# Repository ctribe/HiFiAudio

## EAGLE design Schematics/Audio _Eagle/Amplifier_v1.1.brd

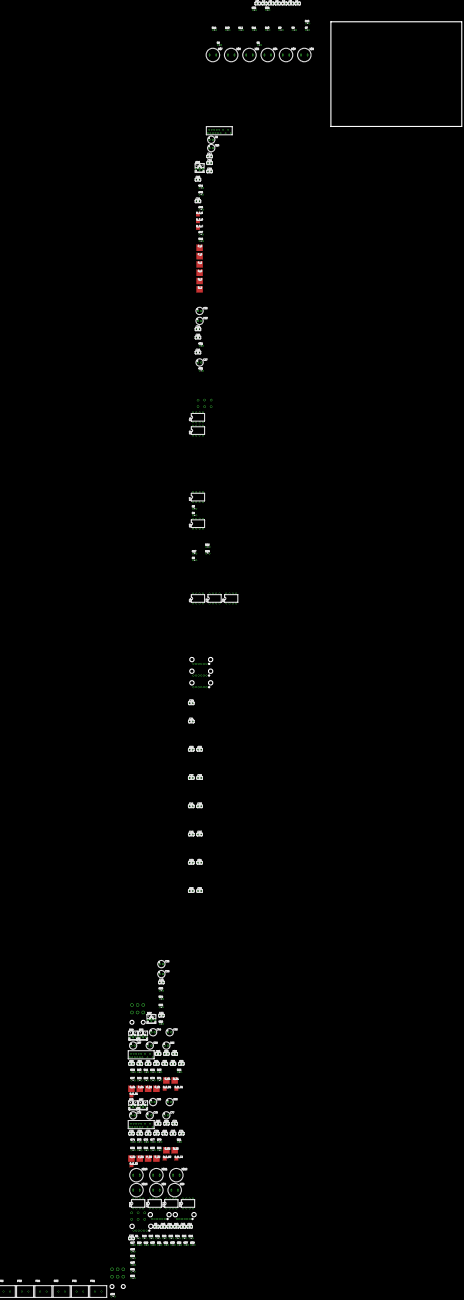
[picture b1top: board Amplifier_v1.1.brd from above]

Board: 2 copper layers, 100.0 x 80.0 mm, 227 parts (0 on the bottom side), 114 nets, no tracks yet.

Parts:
B_R_B, B_R_B1, B_R_B2: SMT_PAD_3MM
B_R_C, B_R_C1, B_R_C2: SMT_PAD_3MM
B_R_E, B_R_E1, B_R_E2: SMT_PAD_3MM
C1, C3, C4, C5, C6, C7, C8, C9, C10, C11, C12, C13, C14, C15: C025-024X044
C2, C16, C22, C23, C27, C36, C38, C44, C46, C57, C58, C62, C65, C66, C72, C73, C77: 100uF; E2,5-6
C17, C18, C24, C25, C26, C29, C31, C33, C35, C37, C39, C40, C41, C42, C43, C45, C47, C48, C49, C50, C51, C53, C55, C59, C60, C61, C63, C64, C67, C68, C74, C75, C76, C78, C79: 0.1uF; C025-024X044
C19, C20, C21, C52, C54, C56, C69, C70, C71: 22pF; C025-024X044
IC1, IC2, IC3, IC4, IC5, IC6, IC7, IC10, IC11, IC12, IC13: NE5532N; DIL08
N_B, N_B1, N_B2: SMT_PAD_5MM
N_D, N_D1, N_D2: SMT_PAD_5MM
N_S, N_S1, N_S2: SMT_PAD_5MM
PR1, PR2, PR3, PR4, PR5, PR6: 0.1; 2-1623788-1
P_B, P_B1, P_B2: SMT_PAD_5MM
P_D, P_D1, P_D2: SMT_PAD_5MM
P_S, P_S1, P_S2: SMT_PAD_5MM
R1, R2, R3, R4, R5, R6, R7, R8, R9, R10, R11, R12, R13, R14, R15, R16, R17, R18, R19, R20, R21, R22, R23, R24, R25, R26, R27, R28, R29, R30, R31, R32, R33, R34, R35, R36, R37, R38, R39, R88, R89, R90, R91, R92: 0204V
R43, R57, R58, R72, R73, R87: B25U
R44, R47, R48, R52, R53, R54, R55, R56, R59, R62, R63, R67, R68, R69, R70, R71, R74, R77, R78, R82, R83, R84, R85, R86: 1.2k; 0204V
R45, R60, R75: 500; 0204V
R46, R61, R76: 12k; 0204V
R51, R66, R81: 10; 0204V
U1, U2, U8: LME49830; NDN0015A
U$1, U$13, U$14, U$19, U$20, U$21: TONE_POT_2GANG
U$2, U$3, U$4, U$5, U$6, U$7, U$8, U$9, U$10, U$11, U$12, U$15: INDUCTOR
U$16, U$18: VOL_POT_2GANG
U$17, U$22: MOLEX_6P

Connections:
+12V: C31.2, C35.2, C36.+, C39.2, C43.2, C47.2, C51.2, C55.2, U$22.P$1
-12V: C29.1, C33.1, C37.1, C38.-, C41.1, C45.1, C49.1, C53.1, U$22.P$6
GND: C2.+, C3.1, C4.1, C7.2, C8.2, C10.1, C11.1, C14.2, C15.2, C16.-, C17.1, C18.2, C22.-, C23.+, C24.2, C25.1, C26.1, C27.-, C29.2, C31.1, C33.2, C35.1, C36.-, C37.2, C38.+, C39.1, C40.1, C41.2, C42.1, C43.1, C44.+, C45.2, C46.-, C47.1, C48.1, C49.2, C50.2, C51.1, C53.2, C55.1, C57.-, C58.+, C59.2, C60.1, C61.1, C62.-, C63.1, C64.1, C65.+, C66.-, C67.1, C68.2, C72.-, C73.+, C74.2, C75.1, C76.1, C77.-, C78.1, C79.1, IC1.4, IC1.5, IC1.8, IC2.4, IC2.5, IC2.8, IC3.4, IC3.5, IC3.8, IC4.4, IC4.8, IC5.4, IC5.8, IC6.4, IC6.8, IC7.3, IC7.4, IC7.8, IC10.5, IC11.5, IC12.3, IC13.5, R3.2, R5.1, R7.1, R10.1, R13.1, R15.1, R20.1, R23.1, R26.1, R28.1, R31.2, R38.1, R53.2, R68.2, R83.2, U1.3, U2.3, U8.3, U$3.1, U$4.1, U$5.1, U$6.1, U$9.1, U$10.1, U$11.1, U$12.1, U$17.P$2, U$17.P$4, U$17.P$6, U$22.P$4
unnamed: IC7.2, R2.2, U$16.1_1
unnamed: C1.1, IC7.1, U$16.1_2, U$16.1_3
unnamed: IC12.2, R1.2, U$18.1_1
unnamed: R48.2, U8.14
unnamed: C9.1, IC12.1, U$18.1_2, U$18.1_3
unnamed: IC1.2, R7.2, R8.1
unnamed: C4.2, IC1.3, R3.1, U$2.1
unnamed: B_R_C1.PAD, C54.2, R58.E, R59.1
unnamed: IC2.2, R12.1, R13.2
unnamed: R54.2, R88.2, R89.2, R90.2
unnamed: IC1.6, R6.2, R34.1
unnamed: C3.2, R4.2, U$2.2
unnamed: C5.2, R9.2, U$3.2
unnamed: C11.2, IC10.3, R31.1, U$8.1
unnamed: IC3.1, R16.1, R17.2
unnamed: C40.2, R53.1, R54.1, U8.4
unnamed: IC2.1, R11.1, R12.2
unnamed: IC2.6, R11.2, R35.1
unnamed: IC3.6, R16.2, R18.1
unnamed: B_R_B1.PAD, C54.1, R58.A, R58.S, R60.2
unnamed: IC3.7, R88.1, U$14.1_2, U$14.1_3
unnamed: C1.2, R4.1, R9.1, R14.1
unnamed: C7.1, R14.2, U$6.2, U$7.2
unnamed: R18.2, U$14.1_1
unnamed: IC10.6, R19.2, R29.1
unnamed: R2.1, U$22.P$3
unnamed: IC3.2, R5.2, R17.1
unnamed: C52.2, R59.2, U1.12
unnamed: C6.1, U$7.1
unnamed: C12.2, R22.2, U$9.2
unnamed: R55.1, R57.A, U8.5
unnamed: IC11.1, R24.1, R25.2
unnamed: IC11.6, R24.2, R30.1
unnamed: C14.1, R27.2, U$12.2, U$15.2
unnamed: C13.1, U$15.1
unnamed: C42.2, R55.2
unnamed: R29.2, U$19.1_1
unnamed: R39.1, R84.2, R91.2, R92.2
unnamed: B_R_E1.PAD, C52.1, C56.1, R60.1, U1.11
unnamed: R56.2, R57.E, R57.S
unnamed: IC11.7, R91.1, U$20.1_2, U$20.1_3
unnamed: R30.2, U$20.1_1
unnamed: IC10.1, R19.1, R21.2
unnamed: C10.2, R32.2, U$8.2
unnamed: IC10.2, R20.2, R21.1
unnamed: IC11.2, R25.1, R26.2
unnamed: IC13.1, R33.1, R36.2
unnamed: C56.2, U1.6
unnamed: IC13.6, R33.2, R37.1
unnamed: IC13.7, R92.1, U$21.1_2, U$21.1_3
unnamed: R62.2, U1.13
unnamed: P_B1.PAD, R61.2, R63.1
unnamed: R34.2, U$1.1_1
unnamed: IC1.7, R90.1, U$1.1_2, U$1.1_3
unnamed: IC2.7, R89.1, U$13.1_2, U$13.1_3
unnamed: R35.2, U$13.1_1
unnamed: R37.2, U$21.1_1
unnamed: IC13.2, R36.1, R38.2
unnamed: C13.2, C15.1, IC13.3, R28.2, U$11.2
unnamed: C9.2, R22.1, R27.1, R32.1
unnamed: C12.1, IC11.3, R23.2, U$10.2
unnamed: N_B1.PAD, R61.1, R62.1
unnamed: C5.1, IC2.3, R10.2, U$4.2
unnamed: IC10.7, R39.2, R69.2, U$19.1_2, U$19.1_3
unnamed: B_R_C.PAD, C20.2, R43.E, R44.1
unnamed: C21.2, U8.6
unnamed: B_R_E.PAD, C19.1, C21.1, R45.1, U8.11
unnamed: B_R_B.PAD, C20.1, R43.A, R43.S, R45.2
unnamed: C19.2, R44.2, U8.12
unnamed: R47.2, U8.13
unnamed: PR1.P$4, P_S1.PAD
unnamed: P_B.PAD, R46.2, R48.1
unnamed: N_B.PAD, R46.1, R47.1
unnamed: PR4.P$4, P_S.PAD
unnamed: PR3.P$4, PR4.P$3, R51.2, R56.1, U8.8, U$17.P$1
unnamed: PR1.P$3, PR2.P$4, R66.2, R71.1, U1.8, U$17.P$3
unnamed: C61.2, R66.1
unnamed: C62.+, R67.2, U1.2
unnamed: R63.2, U1.14
unnamed: C63.2, R68.1, R69.1, U1.4
unnamed: C64.2, R70.2
unnamed: R70.1, R72.A, U1.5
unnamed: R71.2, R72.E, R72.S
unnamed: C26.2, R51.1
unnamed: C27.+, R52.2, U8.2
unnamed: B_R_C2.PAD, C70.2, R73.E, R74.1
unnamed: B_R_B2.PAD, C70.1, R73.A, R73.S, R75.2
unnamed: IC1.1, R6.1, R8.2
unnamed: C69.2, R74.2, U2.12
unnamed: B_R_E2.PAD, C69.1, C71.1, R75.1, U2.11
unnamed: C71.2, U2.6
unnamed: R77.2, U2.13
unnamed: P_B2.PAD, R76.2, R78.1
unnamed: N_B2.PAD, R76.1, R77.1
unnamed: PR5.P$4, P_S2.PAD
unnamed: PR5.P$3, PR6.P$4, R81.2, R86.1, U2.8, U$17.P$5
unnamed: C76.2, R81.1
unnamed: C77.+, R82.2, U2.2
unnamed: R78.2, U2.14
unnamed: C78.2, R83.1, R84.1, U2.4
unnamed: C79.2, R85.2
unnamed: R85.1, R87.A, U2.5
unnamed: R86.2, R87.E, R87.S
unnamed: C6.2, C8.1, IC3.3, R15.2, U$5.2
unnamed: N_S1.PAD, PR2.P$3
unnamed: R1.1, U$22.P$5
unnamed: N_S2.PAD, PR6.P$3
unnamed: N_S.PAD, PR3.P$3
V+: C16.+, C18.1, C46.+, C50.1, C66.+, C68.1, U1.15, U2.15, U8.15
V-: C2.-, C17.2, C23.-, C25.2, C44.-, C48.2, C58.-, C60.2, C65.-, C67.2, C73.-, C75.2, IC10.4, IC11.4, IC12.4, IC13.4, N_D.PAD, N_D1.PAD, N_D2.PAD, U1.10, U2.10, U8.10
VCC: C22.+, C24.1, C57.+, C59.1, C72.+, C74.1, IC10.8, IC11.8, IC12.8, IC13.8, P_D.PAD, P_D1.PAD, P_D2.PAD

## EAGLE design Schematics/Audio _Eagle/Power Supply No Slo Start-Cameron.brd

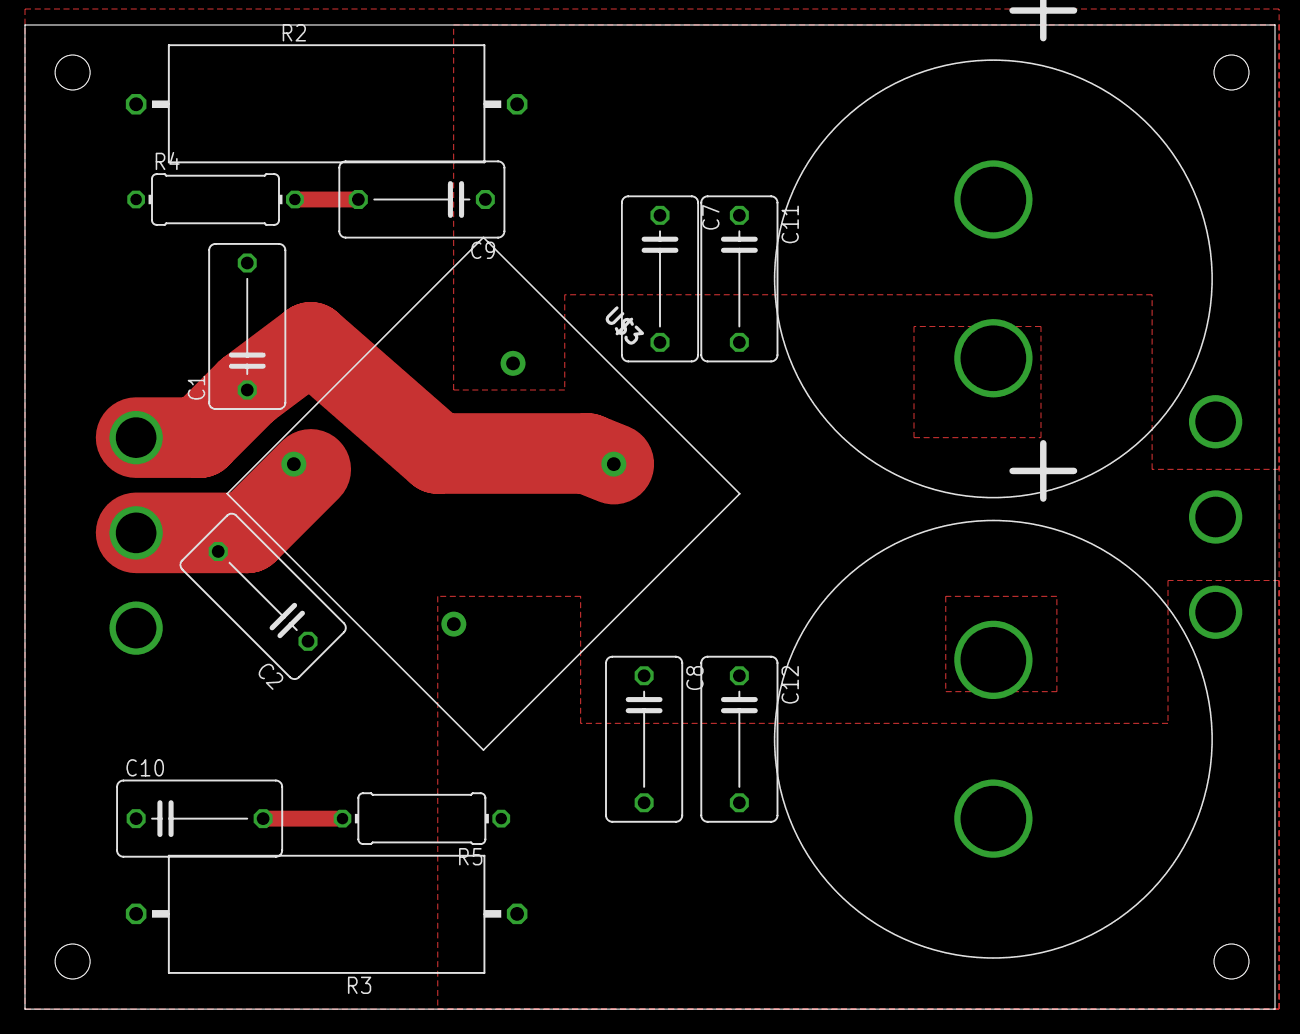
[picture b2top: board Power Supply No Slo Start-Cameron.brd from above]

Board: 2 copper layers, 100.0 x 78.7 mm, 17 parts (0 on the bottom side), 7 nets.

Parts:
C1, C2, C7, C8, C9, C10: 0.1uF; C102-064X133
C11, C12: 1uF; C102-064X133
C13, C19: 15,000uF; PHI-35
P1, P2: 3PIN_3.25MM; 3PIN_SCREW_EYELET
R2, R3: 2k; VTA52
R4, R5: 1; 0411/12
U$3: GBPC3510W

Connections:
AC1: C1.1, P1.P$1, U$3.AC1
AC2: C2.2, P1.P$2, U$3.AC2
GND: C1.2, C2.1, C7.2, C8.1, C10.1, C11.2, C12.1, C13.+, C19.-, P1.P$3, P2.P$2, R2.1, R3.2, R4.1
unnamed: C10.2, R5.2
unnamed: C9.2, R4.2
VCC: C7.1, C9.1, C11.1, C19.+, P2.P$1, R2.2, U$3.V+
VEE: C8.2, C12.2, C13.-, P2.P$3, R3.1, R5.1, U$3.V-

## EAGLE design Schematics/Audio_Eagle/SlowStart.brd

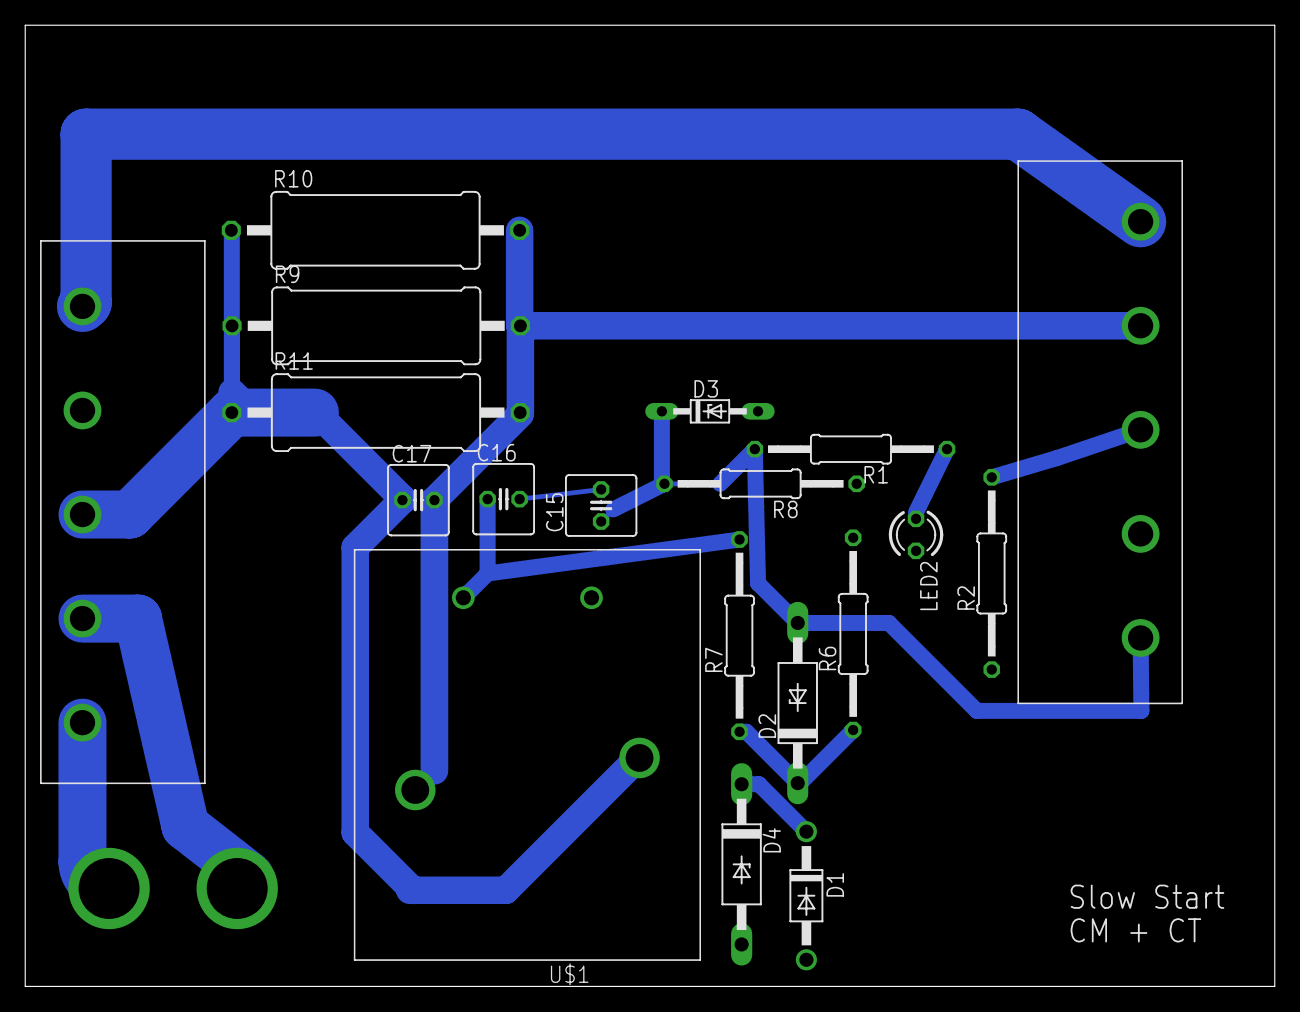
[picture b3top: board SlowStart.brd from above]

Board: 2 copper layers, 99.1 x 76.2 mm, 20 parts (0 on the bottom side), 11 nets.

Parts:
C15, C16: 1uF; C025-060X050
C17: 0.01uF; C025-060X050
D1: 1N4004; DO41-10
D2: 22V; P1Z12
D3: 3.9V; DO34Z7
D4: 28V; P1Z12
LED2: TLLG4400; LED3MM
R1, R8: 10k; 0207/15
R2: 100; 0207/15
R6: 560; 0207/15
R7: 390; 0207/15
R9, R10, R11: 68; 0617/22
U$1: T9AS1D; RELAY_CM
U$2, U$3: SCREW_TERMINAL_5
U$4: FUSE; FUSE_PADS

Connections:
GND: C15.2, C16.2, D1.A, D3.A, D4.A, LED2.K, R2.1, R8.1, U$1.COIL+, U$2.P$2
unnamed: LED2.A, R1.1
unnamed: U$2.P$6, U$4.P$2
unnamed: R2.2, U$3.P$3
unnamed: U$2.P$5, U$4.P$1
unnamed: C17.2, R9.2, R10.2, R11.2, U$1.NO, U$3.P$5
unnamed: C16.1, D1.C, D4.C, R7.2, U$1.COIL-
unnamed: D2.C, R6.1, R7.1
unnamed: C15.1, D2.A, D3.C, R1.2, R8.2, U$3.P$4
VAC+: U$2.P$4, U$3.P$6
VAC-: C17.1, R9.1, R10.1, R11.1, U$1.COM, U$2.P$3

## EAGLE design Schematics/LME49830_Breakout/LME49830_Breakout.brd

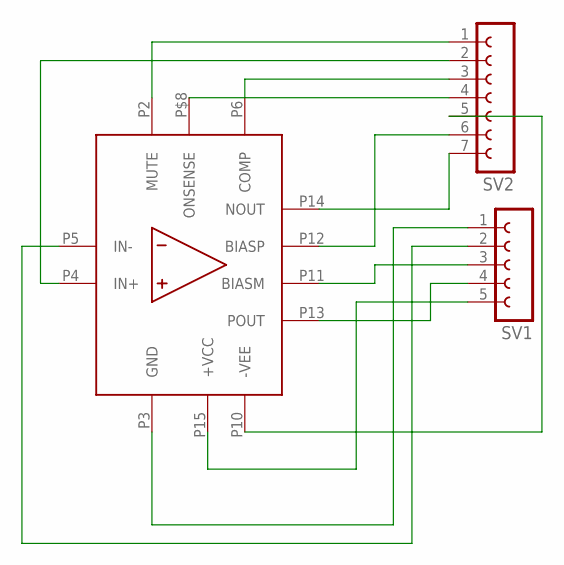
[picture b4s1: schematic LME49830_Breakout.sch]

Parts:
SV1: FE05-1
SV2: FE07-1; FE07
U$1: LME49830; NDN0015A

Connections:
unnamed: SV1.1, U$1.P3 (GND)
unnamed: SV1.2, U$1.P5 (IN-)
unnamed: SV1.3, U$1.P11 (BIASM)
unnamed: SV1.4, U$1.P13 (POUT)
unnamed: SV1.5, U$1.P15 (+VCC)
unnamed: SV2.1, U$1.P2 (MUTE)
unnamed: SV2.2, U$1.P4 (IN+)
unnamed: SV2.3, U$1.P6 (COMP)
unnamed: SV2.4, U$1.P$8 (ONSENSE)
unnamed: SV2.5, U$1.P10 (-VEE)
unnamed: SV2.6, U$1.P12 (BIASP)
unnamed: SV2.7, U$1.P14 (NOUT)

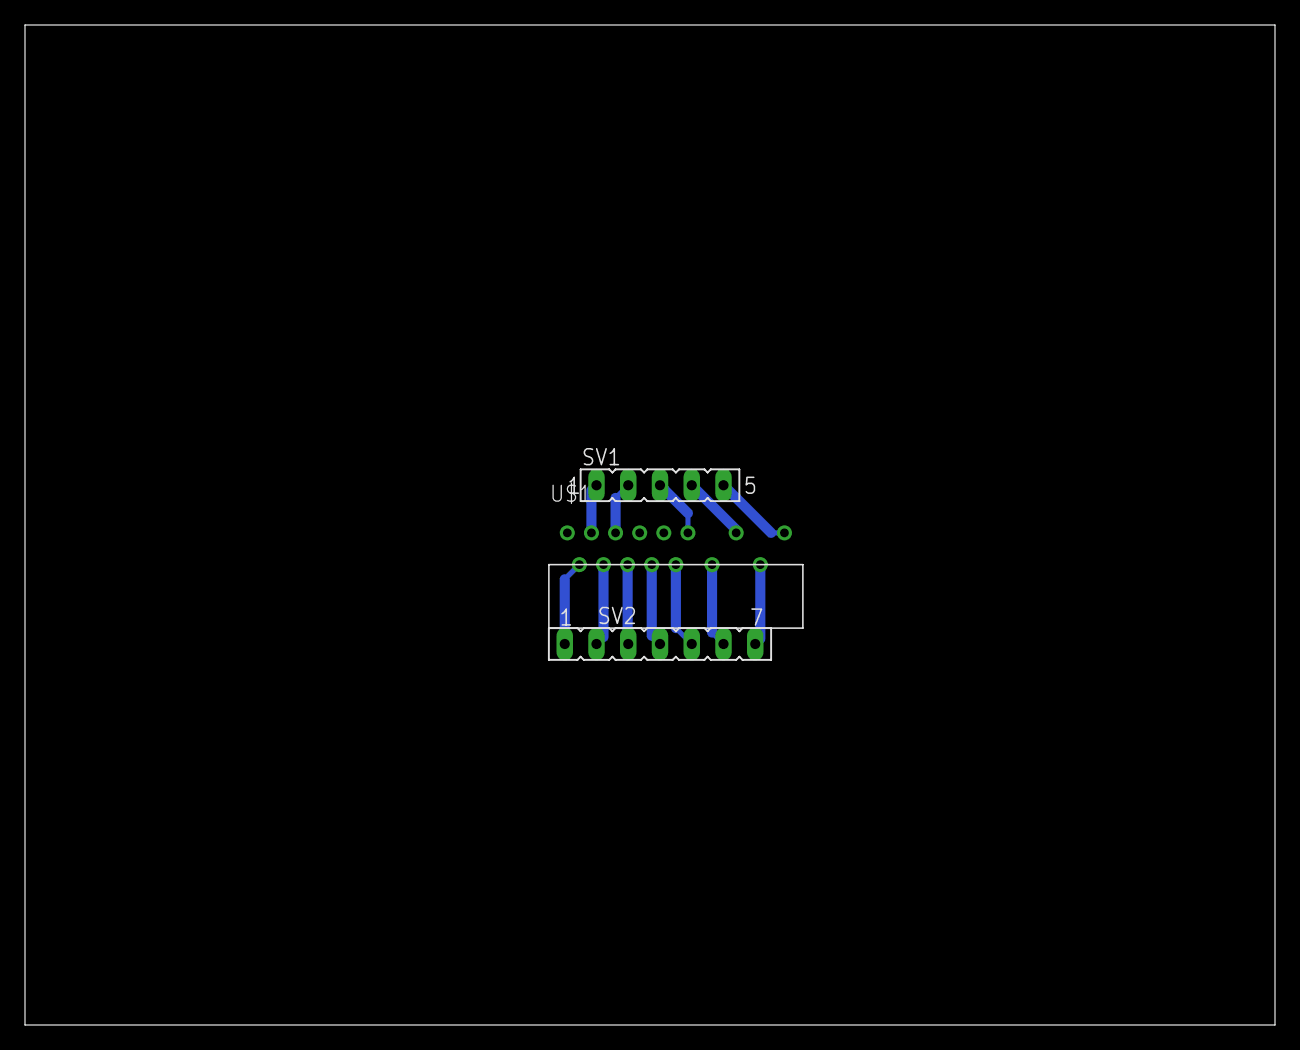
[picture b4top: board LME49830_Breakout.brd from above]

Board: 2 copper layers, 100.0 x 80.0 mm, 3 parts (0 on the bottom side), 12 nets.

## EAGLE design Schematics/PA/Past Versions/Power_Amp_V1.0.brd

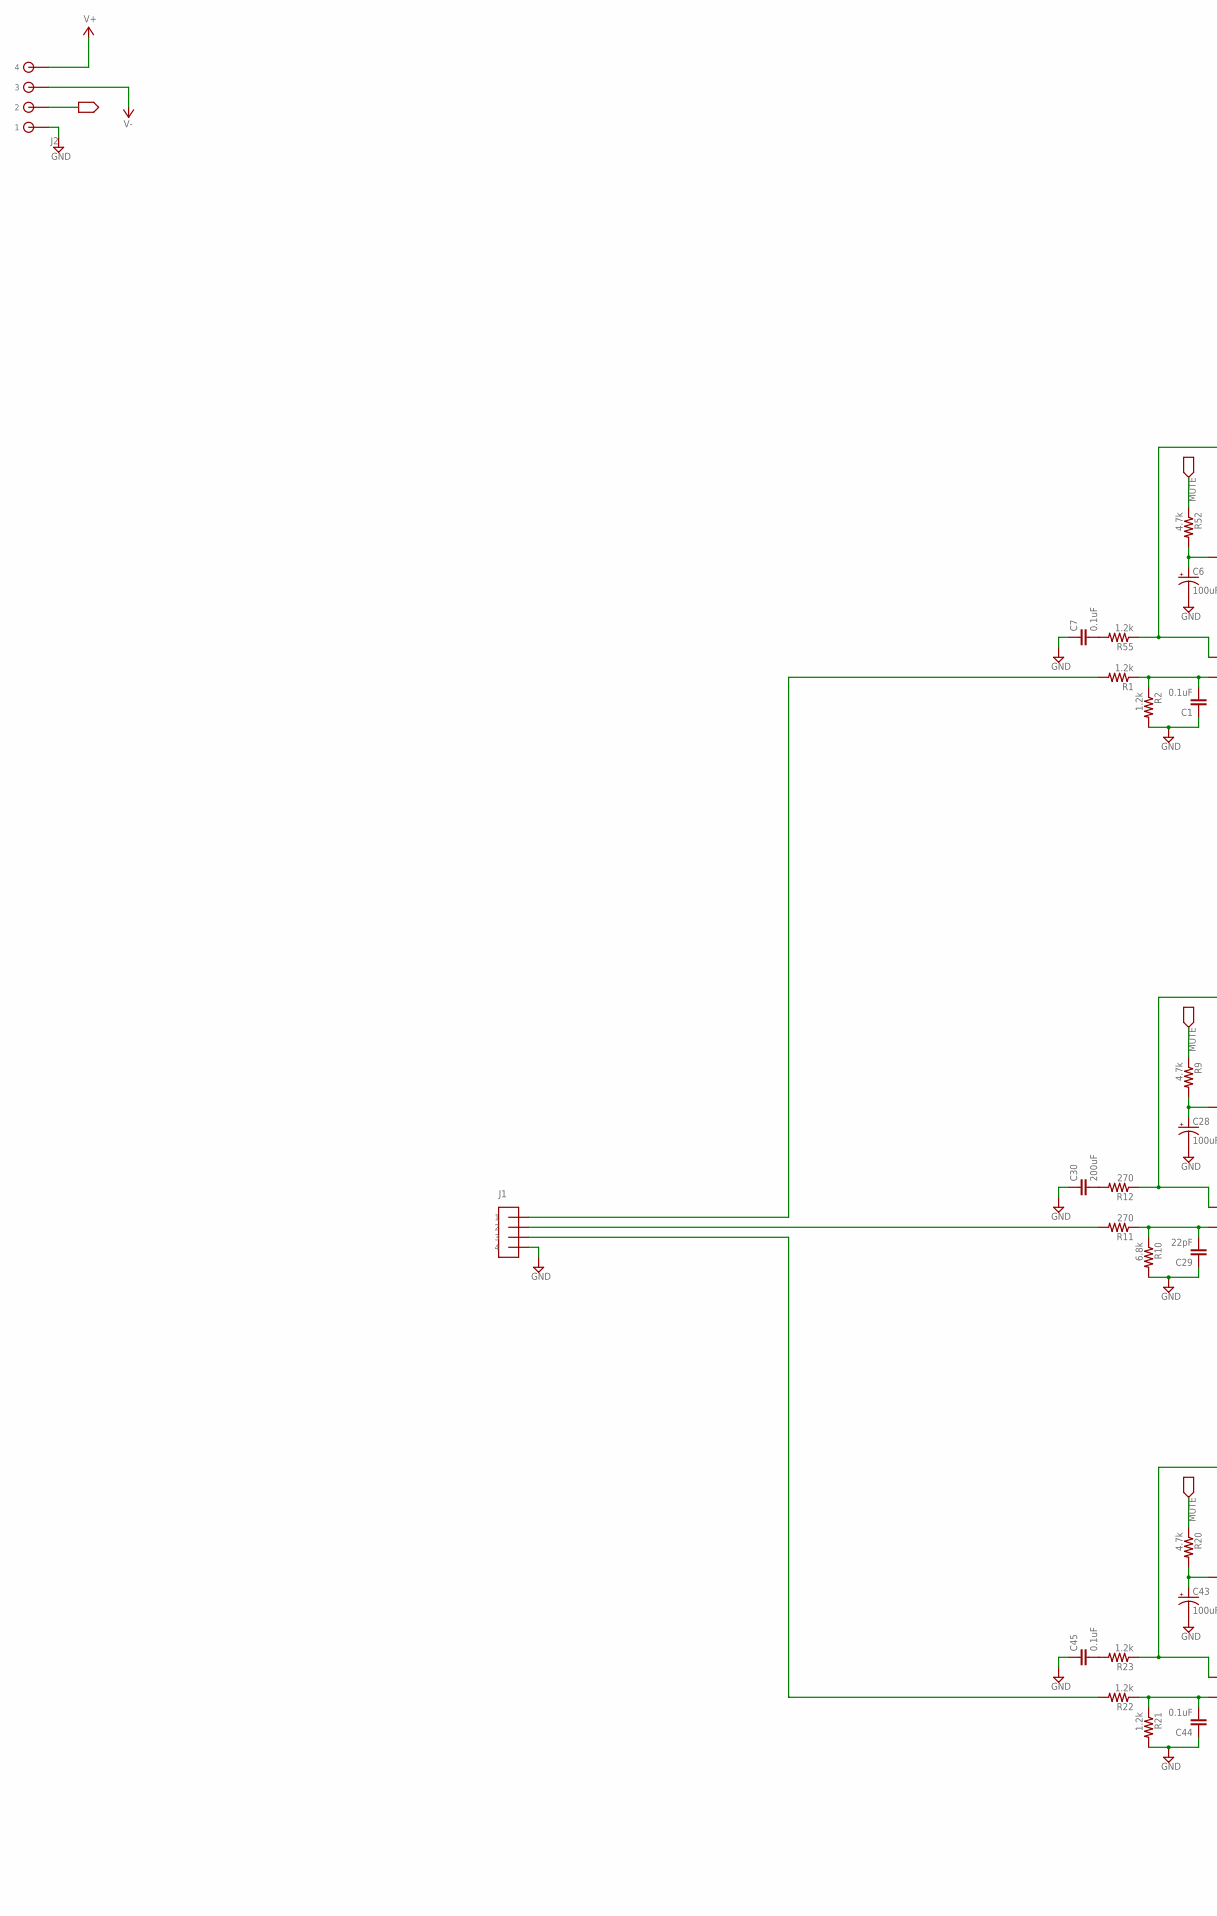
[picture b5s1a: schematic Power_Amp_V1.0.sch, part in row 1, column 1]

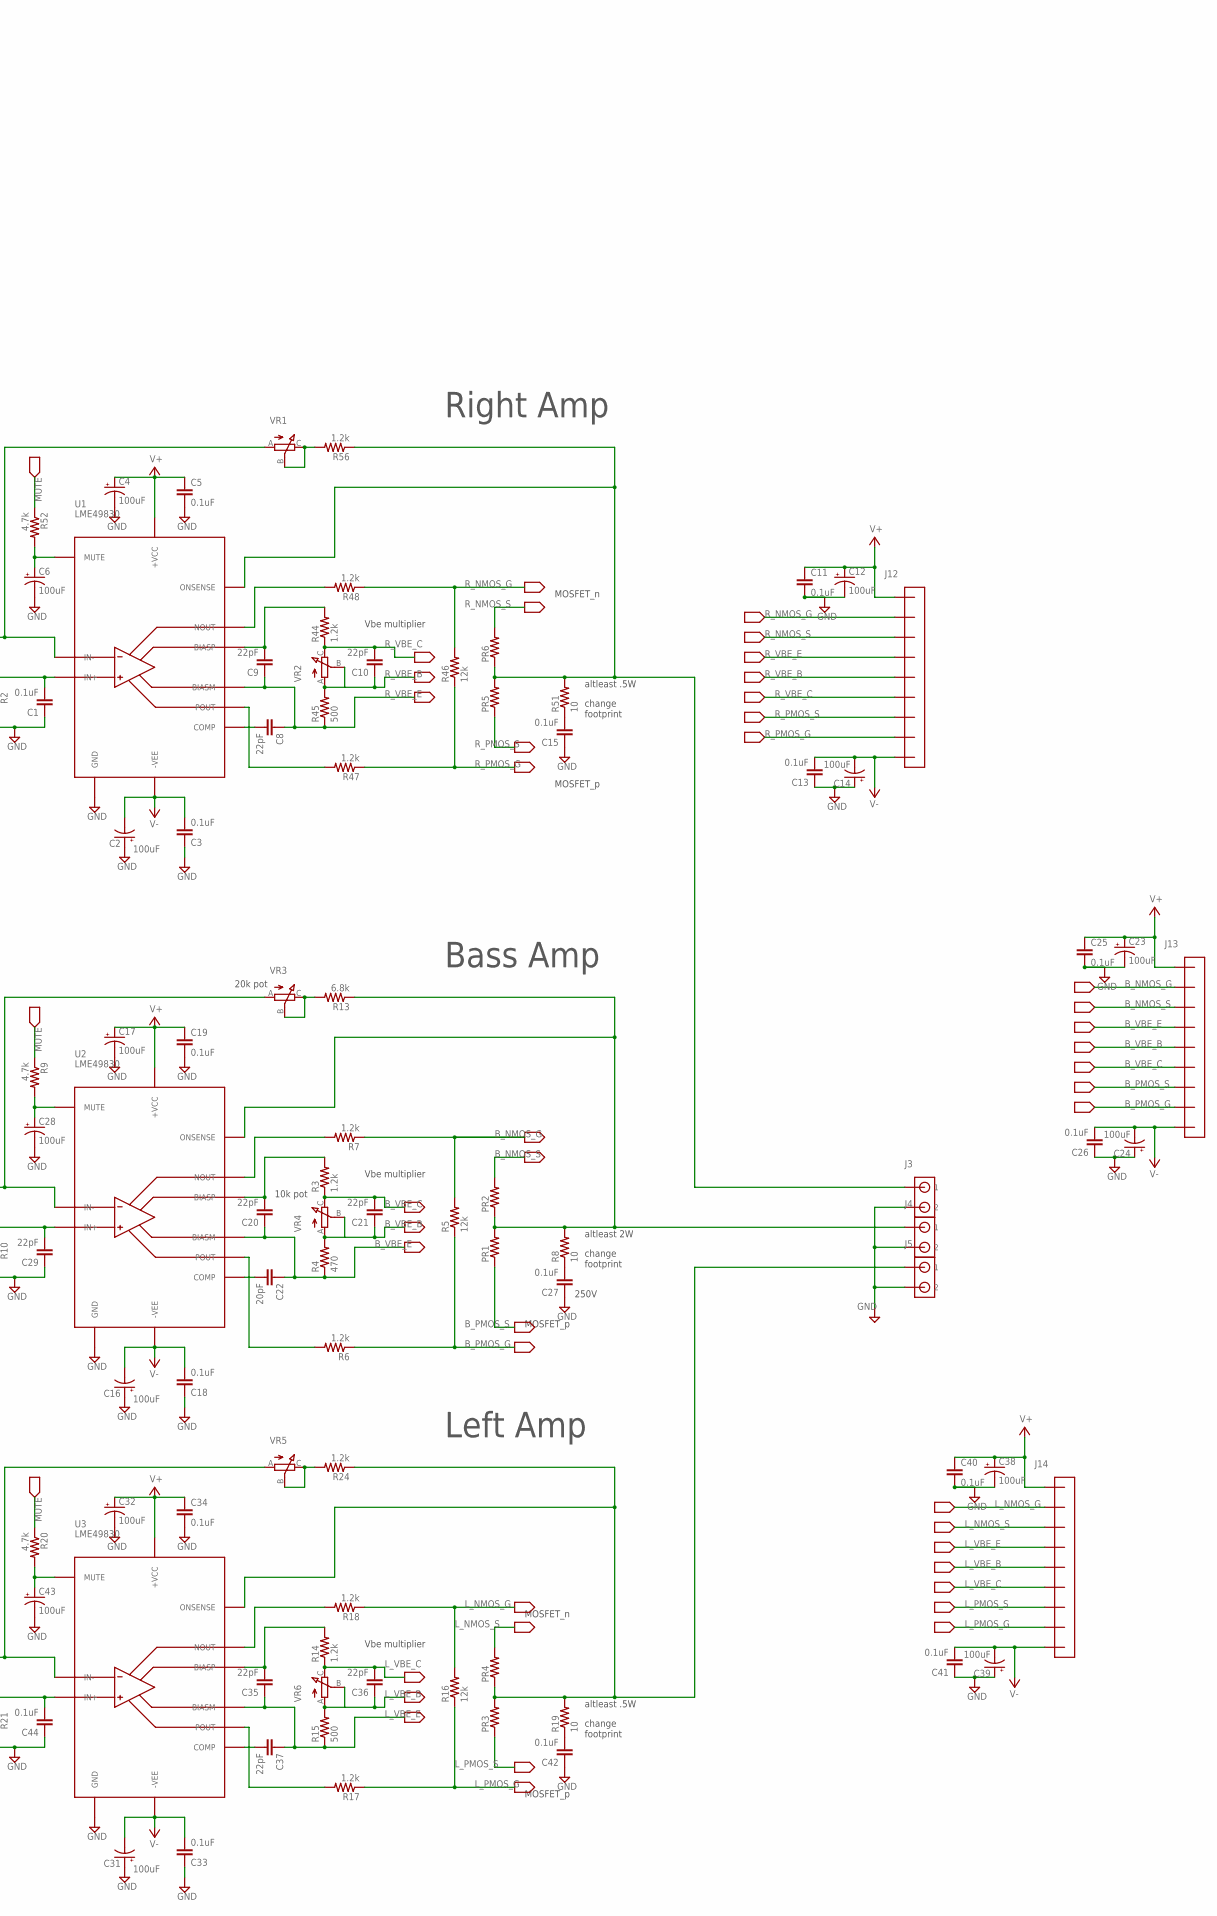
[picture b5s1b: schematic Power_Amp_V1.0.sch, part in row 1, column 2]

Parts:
C1, C3, C5, C7, C11, C13, C15, C18, C19, C25, C26, C27, C33, C34, C40, C41, C42, C44, C45: 0.1uF; C050-024X044
C2, C4, C6, C12, C14, C16, C17, C23, C24, C28, C31, C32, C38, C39, C43: 100uF; E2,5-6
C8, C9, C10, C20, C21, C29, C35, C36, C37: 22pF; C050-024X044
C22: 20pF; C050-024X044
C30: 200uF; C050-024X044
J1: 4_PIN_AMPCONN; 4_PIN_AMPCON
J2: 1984633
J3, J4, J5: 2TERMINAL_SPEAKER
J12, J13, J14: 1725724
PR1, PR2, PR3, PR4, PR5, PR6: R-US_0617/5V; 0617V
R1, R2, R3, R6, R7, R14, R17, R18, R21, R22, R23, R24, R44, R47, R48, R55, R56: 1.2k; 0204V
R4: 470; 0204V
R5, R16, R46: 12k; 0204V
R8, R19, R51: 10; 0309V
R9, R20, R52: 4.7k; 0204V
R10, R13: 6.8k; 0204V
R11, R12: 270; 0204V
R15, R45: 500; 0204V
U1, U2, U3: LME49830; NDN0015A
VR1, VR2, VR3, VR4, VR5, VR6: EVM2W

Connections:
BASS_IN: J1.2, R11.2
BASS_OUT: J4.P$1 (1), PR1.2, PR2.1, R8.2, R13.1, U2.P$8 (ONSENSE)
B_NMOS_G: J13.P$2 (2), R5.2, R7.1
B_NMOS_S: J13.P$3 (3), PR2.2
B_PMOS_G: J13.P$8 (8), R5.1, R6.1
B_PMOS_S: J13.P$7 (7), PR1.1
B_VBE_B: C21.1, J13.P$5 (5), R4.2, VR4.A, VR4.B
B_VBE_C: C21.2, J13.P$6 (6), R3.1, VR4.C
B_VBE_E: C20.1, C22.1, J13.P$4 (4), R4.1, U2.P11 (BIASM)
GND: C1.1, C2.+, C3.1, C4.-, C5.2, C6.-, C7.1, C11.2, C12.-, C13.1, C14.+, C15.1, C16.+, C17.-, C18.1, C19.2, C23.-, C24.+, C25.2, C26.1, C27.1, C28.-, C29.1, C30.1, C31.+, C32.-, C33.1, C34.2, C38.-, C39.+, C40.2, C41.1, C42.1, C43.-, C44.1, C45.1, J1.4, J2.P$1 (1), J3.P$2 (2), J4.P$2 (2), J5.P$2 (2), R2.2, R10.2, R21.2, U1.P3 (GND), U2.P3 (GND), U3.P3 (GND)
LEFT_IN: J1.3, R22.2
LEFT_OUT: J5.P$1 (1), PR3.2, PR4.1, R19.2, R24.1, U3.P$8 (ONSENSE)
L_NMOS_G: J14.P$2 (2), R16.2, R18.1
L_NMOS_S: J14.P$3 (3), PR4.2
L_PMOS_G: J14.P$8 (8), R16.1, R17.1
L_PMOS_S: J14.P$7 (7), PR3.1
L_VBE_B: C36.1, J14.P$5 (5), R15.2, VR6.A, VR6.B
L_VBE_C: C36.2, J14.P$6 (6), R14.1, VR6.C
L_VBE_E: C35.1, C37.1, J14.P$4 (4), R15.1, U3.P11 (BIASM)
MUTE: J2.P$2 (2), R9.1, R20.1, R52.1
unnamed: C20.2, R3.2, U2.P12 (BIASP)
unnamed: R48.2, U1.P14 (NOUT)
unnamed: C22.2, U2.P6 (COMP)
unnamed: R6.2, U2.P13 (POUT)
unnamed: C27.2, R8.1
unnamed: C28.+, R9.2, U2.P2 (MUTE)
unnamed: R7.2, U2.P14 (NOUT)
unnamed: C1.2, R1.1, R2.1, U1.P4 (IN+)
unnamed: C29.2, R10.1, R11.1, U2.P4 (IN+)
unnamed: C30.2, R12.2
unnamed: R12.1, U2.P5 (IN-), VR3.A
unnamed: R13.2, VR3.B, VR3.C
unnamed: C35.2, R14.2, U3.P12 (BIASP)
unnamed: C37.2, U3.P6 (COMP)
unnamed: R17.2, U3.P13 (POUT)
unnamed: R55.1, U1.P5 (IN-), VR1.A
unnamed: C42.2, R19.1
unnamed: C7.2, R55.2
unnamed: C43.+, R20.2, U3.P2 (MUTE)
unnamed: R18.2, U3.P14 (NOUT)
unnamed: C44.2, R21.1, R22.1, U3.P4 (IN+)
unnamed: R56.2, VR1.B, VR1.C
unnamed: C45.2, R23.2
unnamed: R23.1, U3.P5 (IN-), VR5.A
unnamed: R24.2, VR5.B, VR5.C
unnamed: C8.2, U1.P6 (COMP)
unnamed: C9.2, R44.2, U1.P12 (BIASP)
unnamed: R47.2, U1.P13 (POUT)
unnamed: C15.2, R51.1
unnamed: C6.+, R52.2, U1.P2 (MUTE)
RIGHT_IN: J1.1, R1.2
RIGHT_OUT: J3.P$1 (1), PR5.2, PR6.1, R51.2, R56.1, U1.P$8 (ONSENSE)
R_NMOS_G: J12.P$2 (2), R46.2, R48.1
R_NMOS_S: J12.P$3 (3), PR6.2
R_PMOS_G: J12.P$8 (8), R46.1, R47.1
R_PMOS_S: J12.P$7 (7), PR5.1
R_VBE_B: C10.1, J12.P$5 (5), R45.2, VR2.A, VR2.B
R_VBE_C: C10.2, J12.P$6 (6), R44.1, VR2.C
R_VBE_E: C8.1, C9.1, J12.P$4 (4), R45.1, U1.P11 (BIASM)
V+: C4.+, C5.1, C11.1, C12.+, C17.+, C19.1, C23.+, C25.1, C32.+, C34.1, C38.+, C40.1, J2.P$4 (4), J12.P$1 (1), J13.P$1 (1), J14.P$1 (1), U1.P15 (+VCC), U2.P15 (+VCC), U3.P15 (+VCC)
V-: C2.-, C3.2, C13.2, C14.-, C16.-, C18.2, C24.-, C26.2, C31.-, C33.2, C39.-, C41.2, J2.P$3 (3), J12.P$9 (9), J13.P$9 (9), J14.P$9 (9), U1.P10 (-VEE), U2.P10 (-VEE), U3.P10 (-VEE)

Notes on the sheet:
Vbe multiplier
MOSFET_n
MOSFET_p
change footprint
Right Amp
altleast .5W
Bass Amp
altleast 2W
Left Amp
20k pot
10k pot
250V

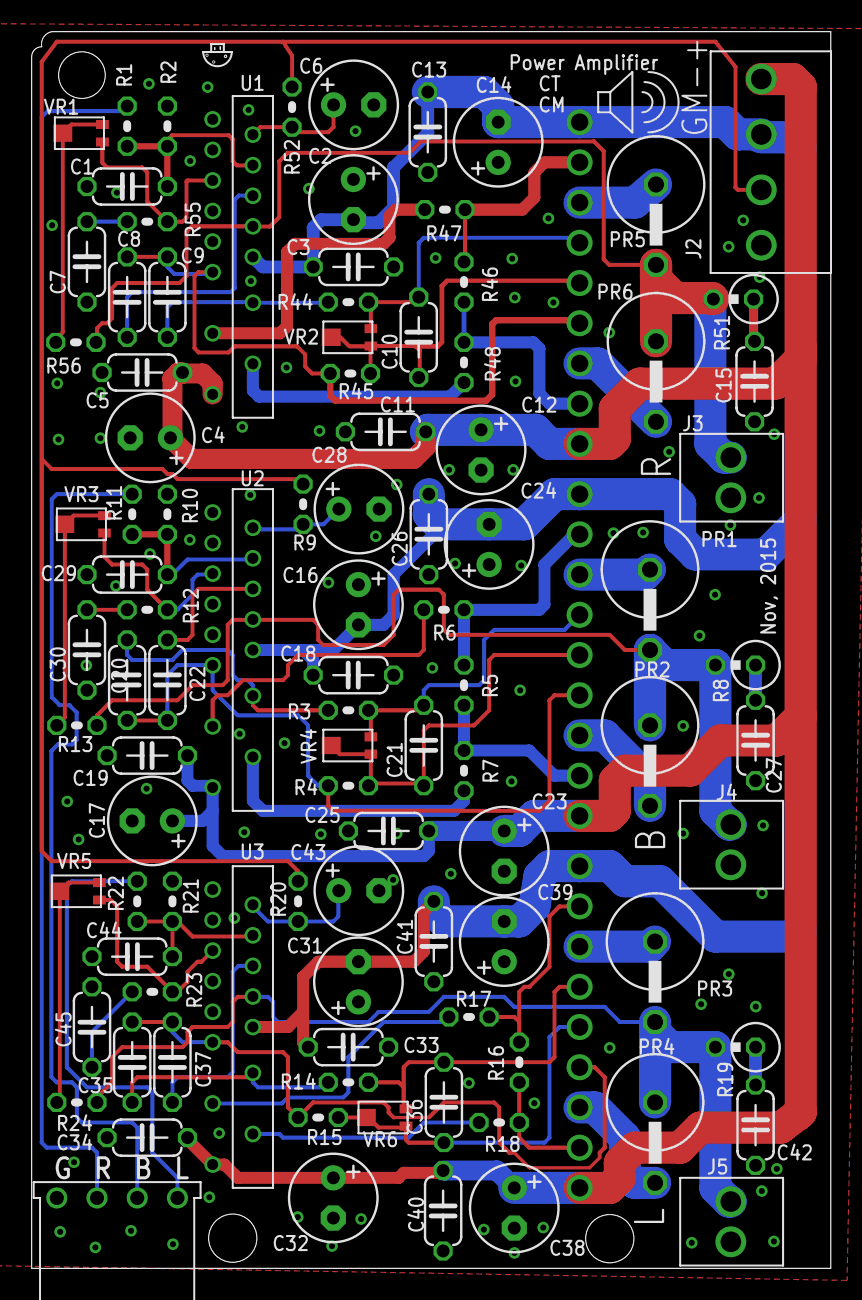
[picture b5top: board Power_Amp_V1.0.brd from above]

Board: 2 copper layers, 50.5 x 78.1 mm, 103 parts (0 on the bottom side), 61 nets.

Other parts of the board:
U$17: MUSHROOM
U$48: SPEAKER

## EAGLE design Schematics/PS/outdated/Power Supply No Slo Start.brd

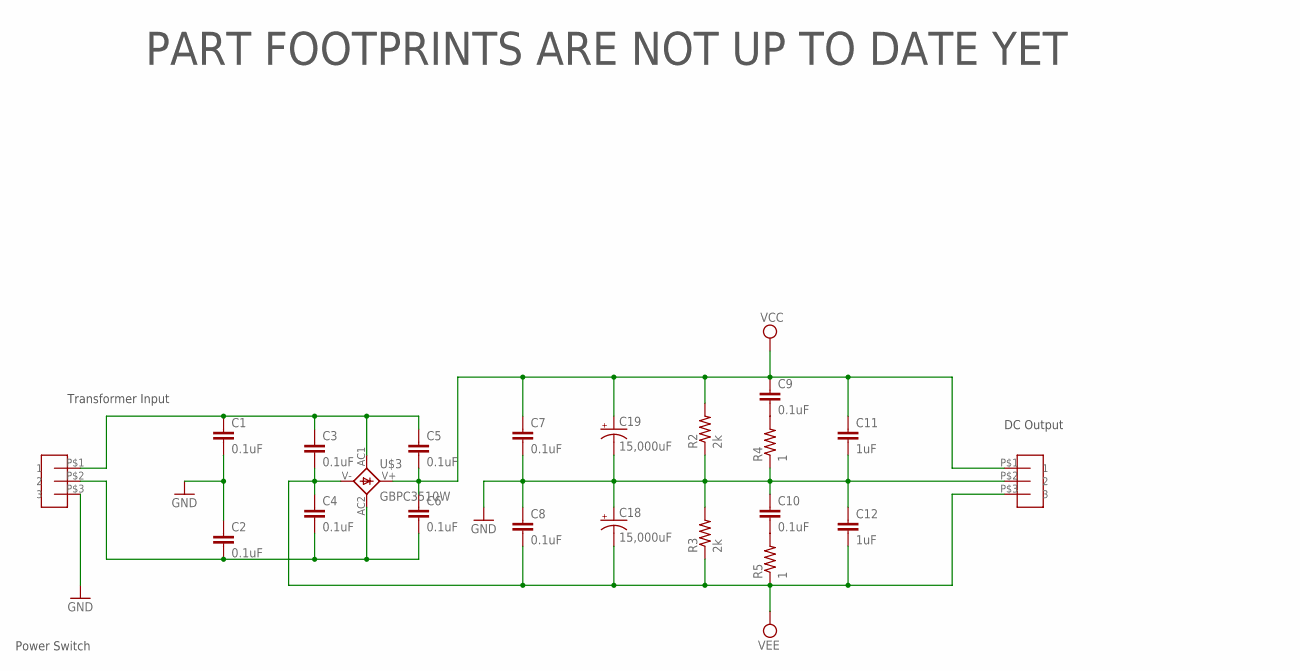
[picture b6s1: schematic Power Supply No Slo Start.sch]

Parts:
C1, C2, C7, C8, C9, C10: 0.1uF; C102-064X133
C3, C4, C5, C6: 0.1uF; C075-052X106
C11, C12: 1uF; C102-064X133
C18, C19: 15,000uF; PHI-35
R2, R3: 2k; VTA52
R4, R5: 1; 0411/12
U$1, U$2: 3PIN_3.25MM; 3PIN_SCREW_EYELET
U$3: GBPC3510W

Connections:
GND: C1.2, C2.1, C7.2, C8.1, C10.1, C11.2, C12.1, C18.+, C19.-, R2.1, R3.2, R4.1, U$1.P$3 (3), U$2.P$2 (2)
unnamed: C10.2, R5.2
unnamed: C9.2, R4.2
unnamed: C2.2, C4.2, C6.2, U$1.P$2 (2), U$3.AC2
unnamed: C1.1, C3.1, C5.1, U$1.P$1 (1), U$3.AC1
VCC: C5.2, C6.1, C7.1, C9.1, C11.1, C19.+, R2.2, U$2.P$1 (1), U$3.V+ (+)
VEE: C3.2, C4.1, C8.2, C12.2, C18.-, R3.1, R5.1, U$2.P$3 (3), U$3.V- (-)

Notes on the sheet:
PART FOOTPRINTS ARE NOT UP TO DATE YET
Transformer Input
DC Output
Power Switch

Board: 2 copper layers, 21 parts (0 on the bottom side), 7 nets, no tracks yet.
